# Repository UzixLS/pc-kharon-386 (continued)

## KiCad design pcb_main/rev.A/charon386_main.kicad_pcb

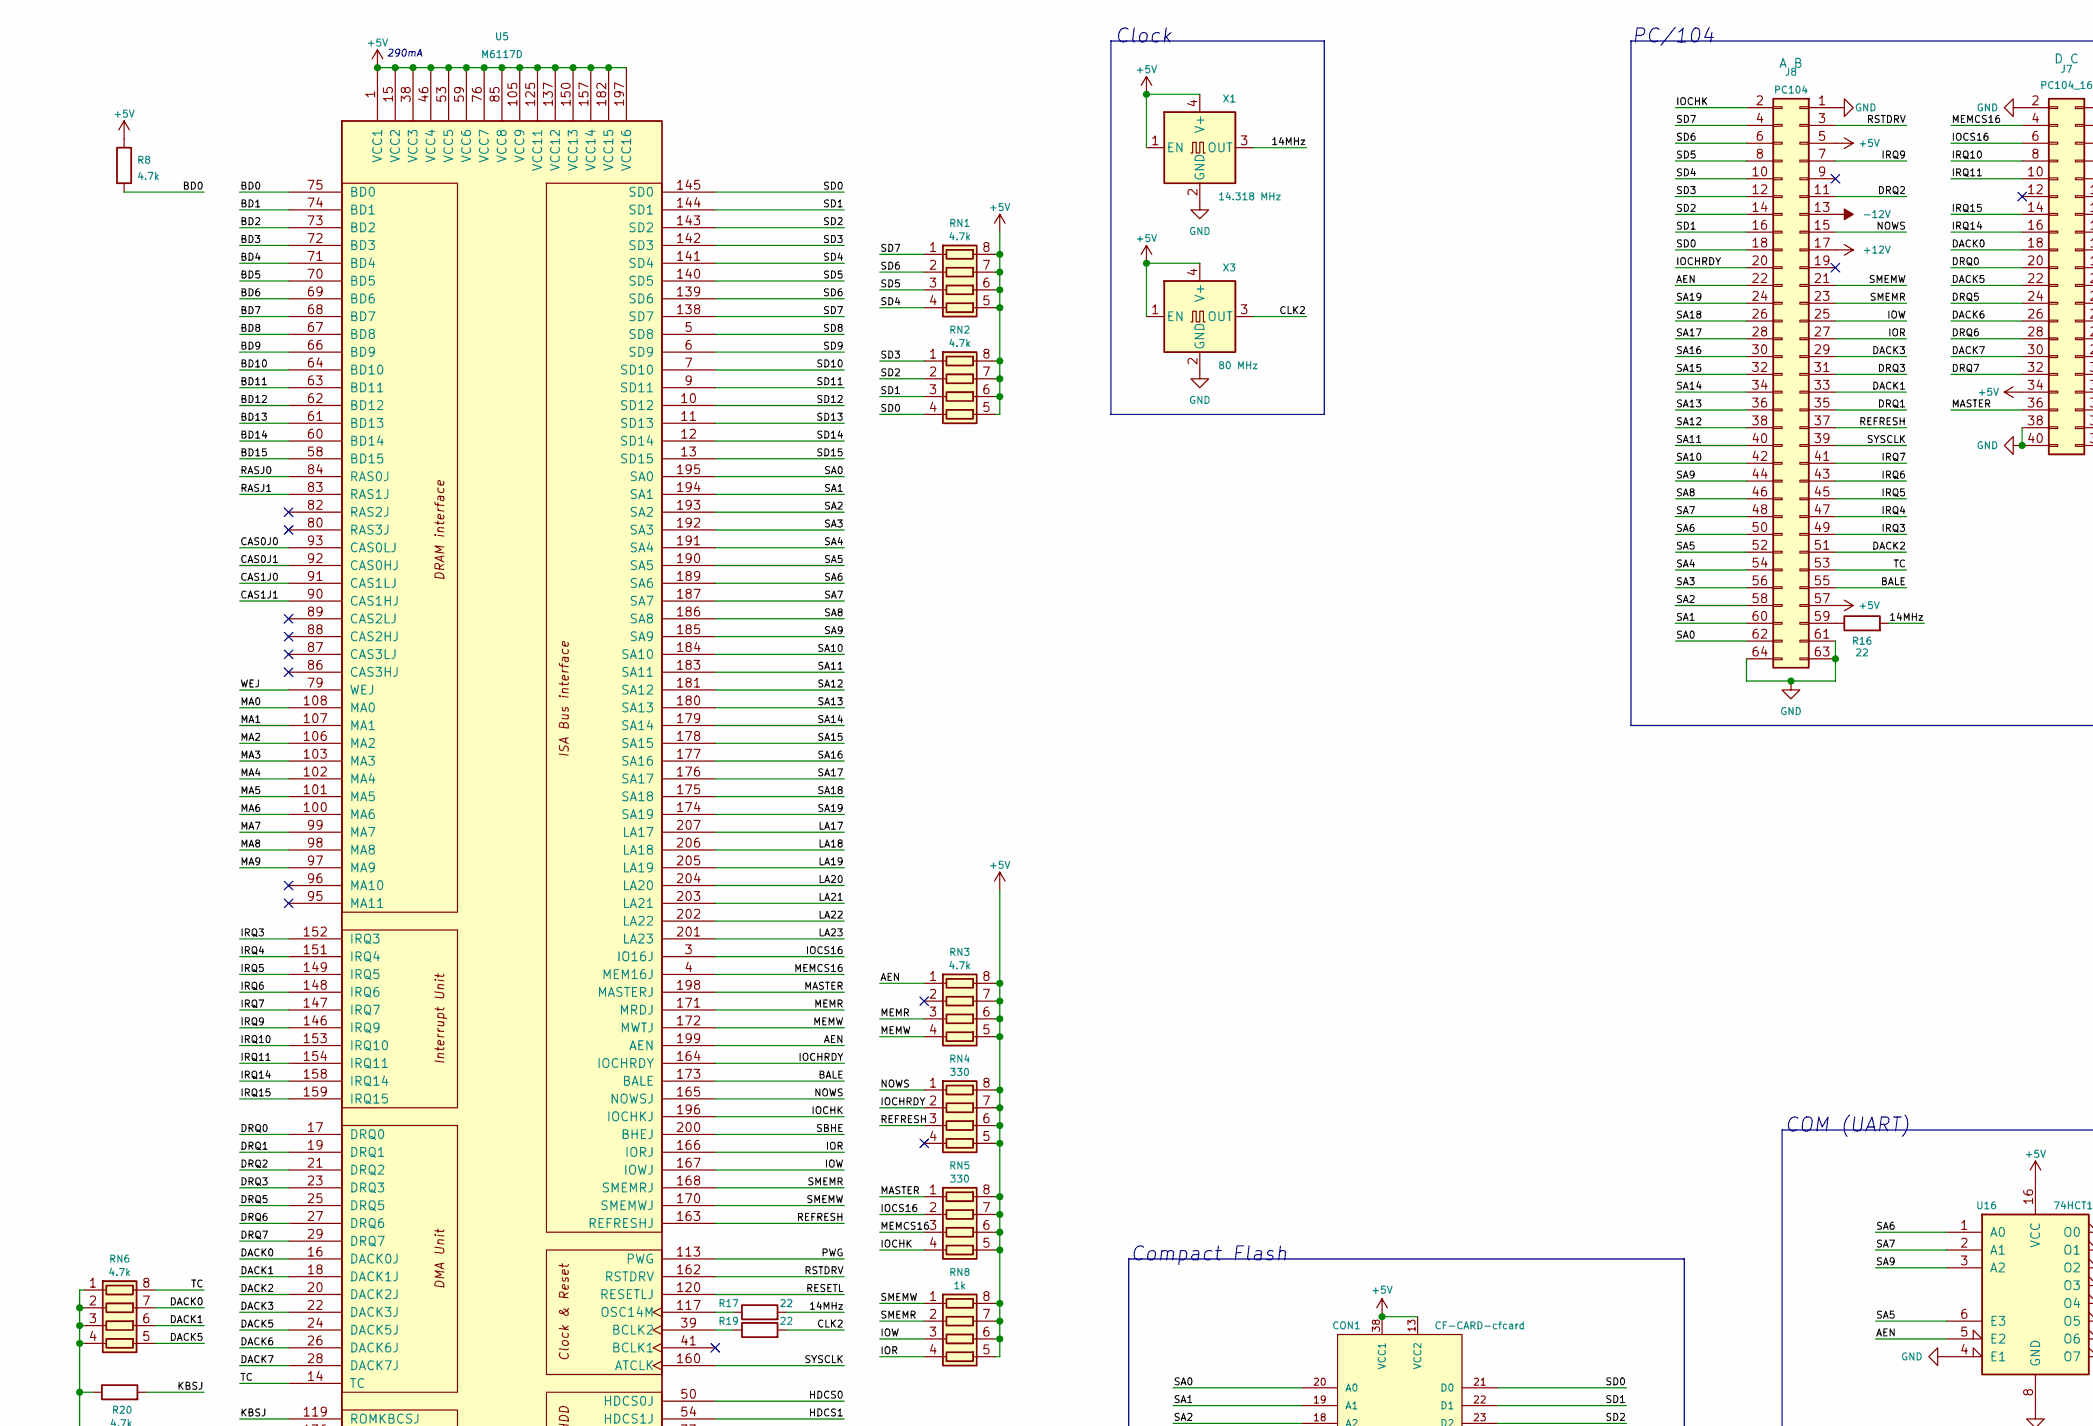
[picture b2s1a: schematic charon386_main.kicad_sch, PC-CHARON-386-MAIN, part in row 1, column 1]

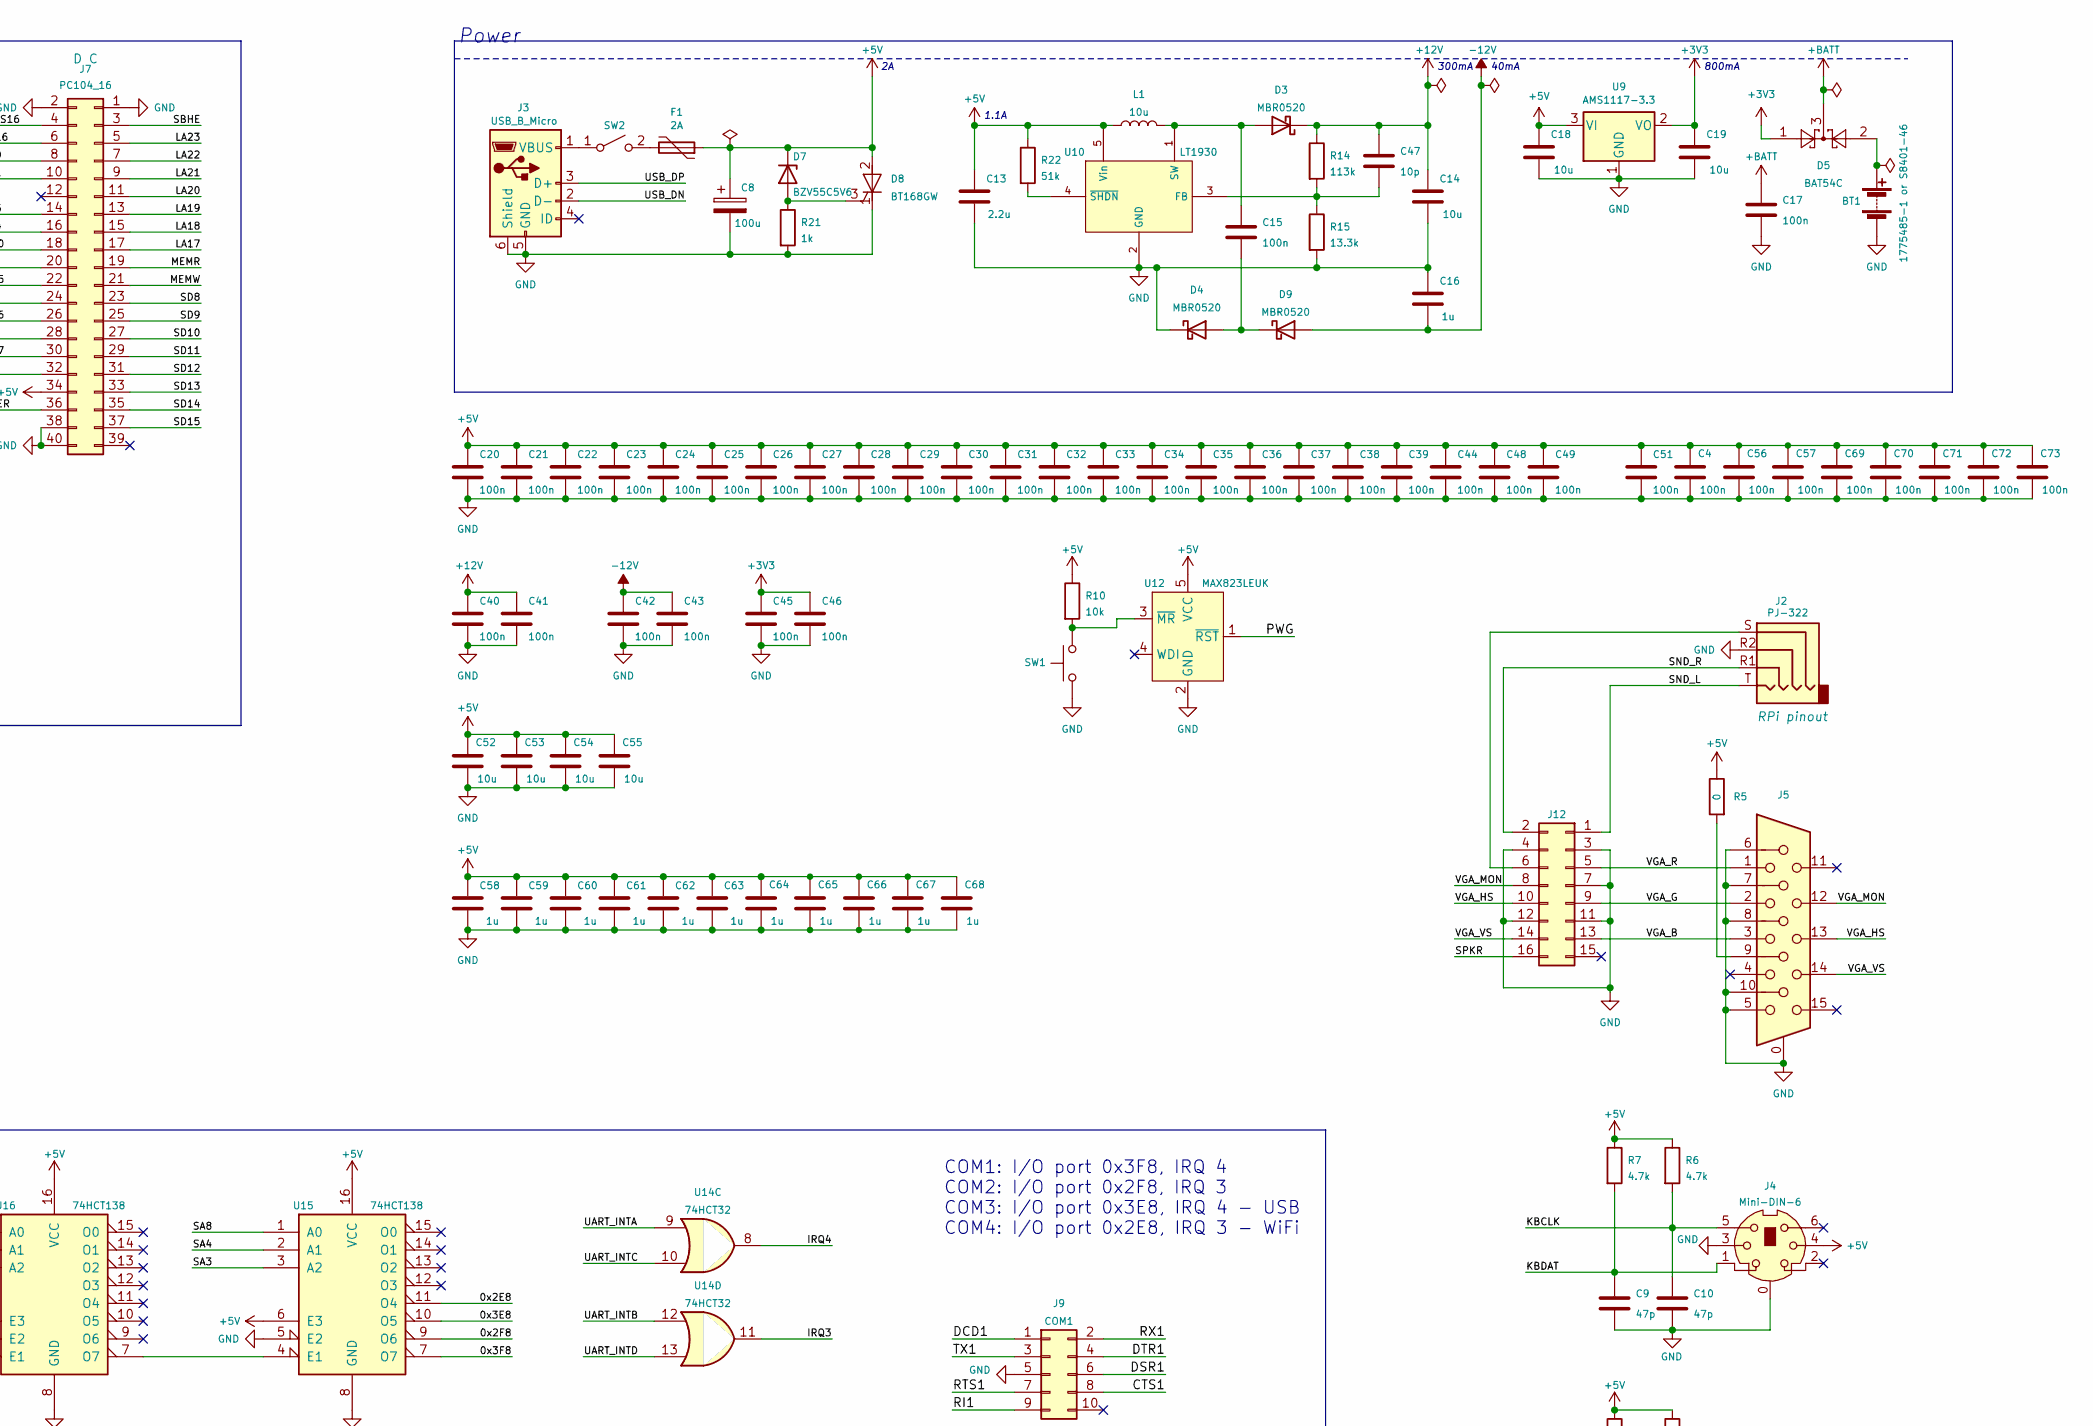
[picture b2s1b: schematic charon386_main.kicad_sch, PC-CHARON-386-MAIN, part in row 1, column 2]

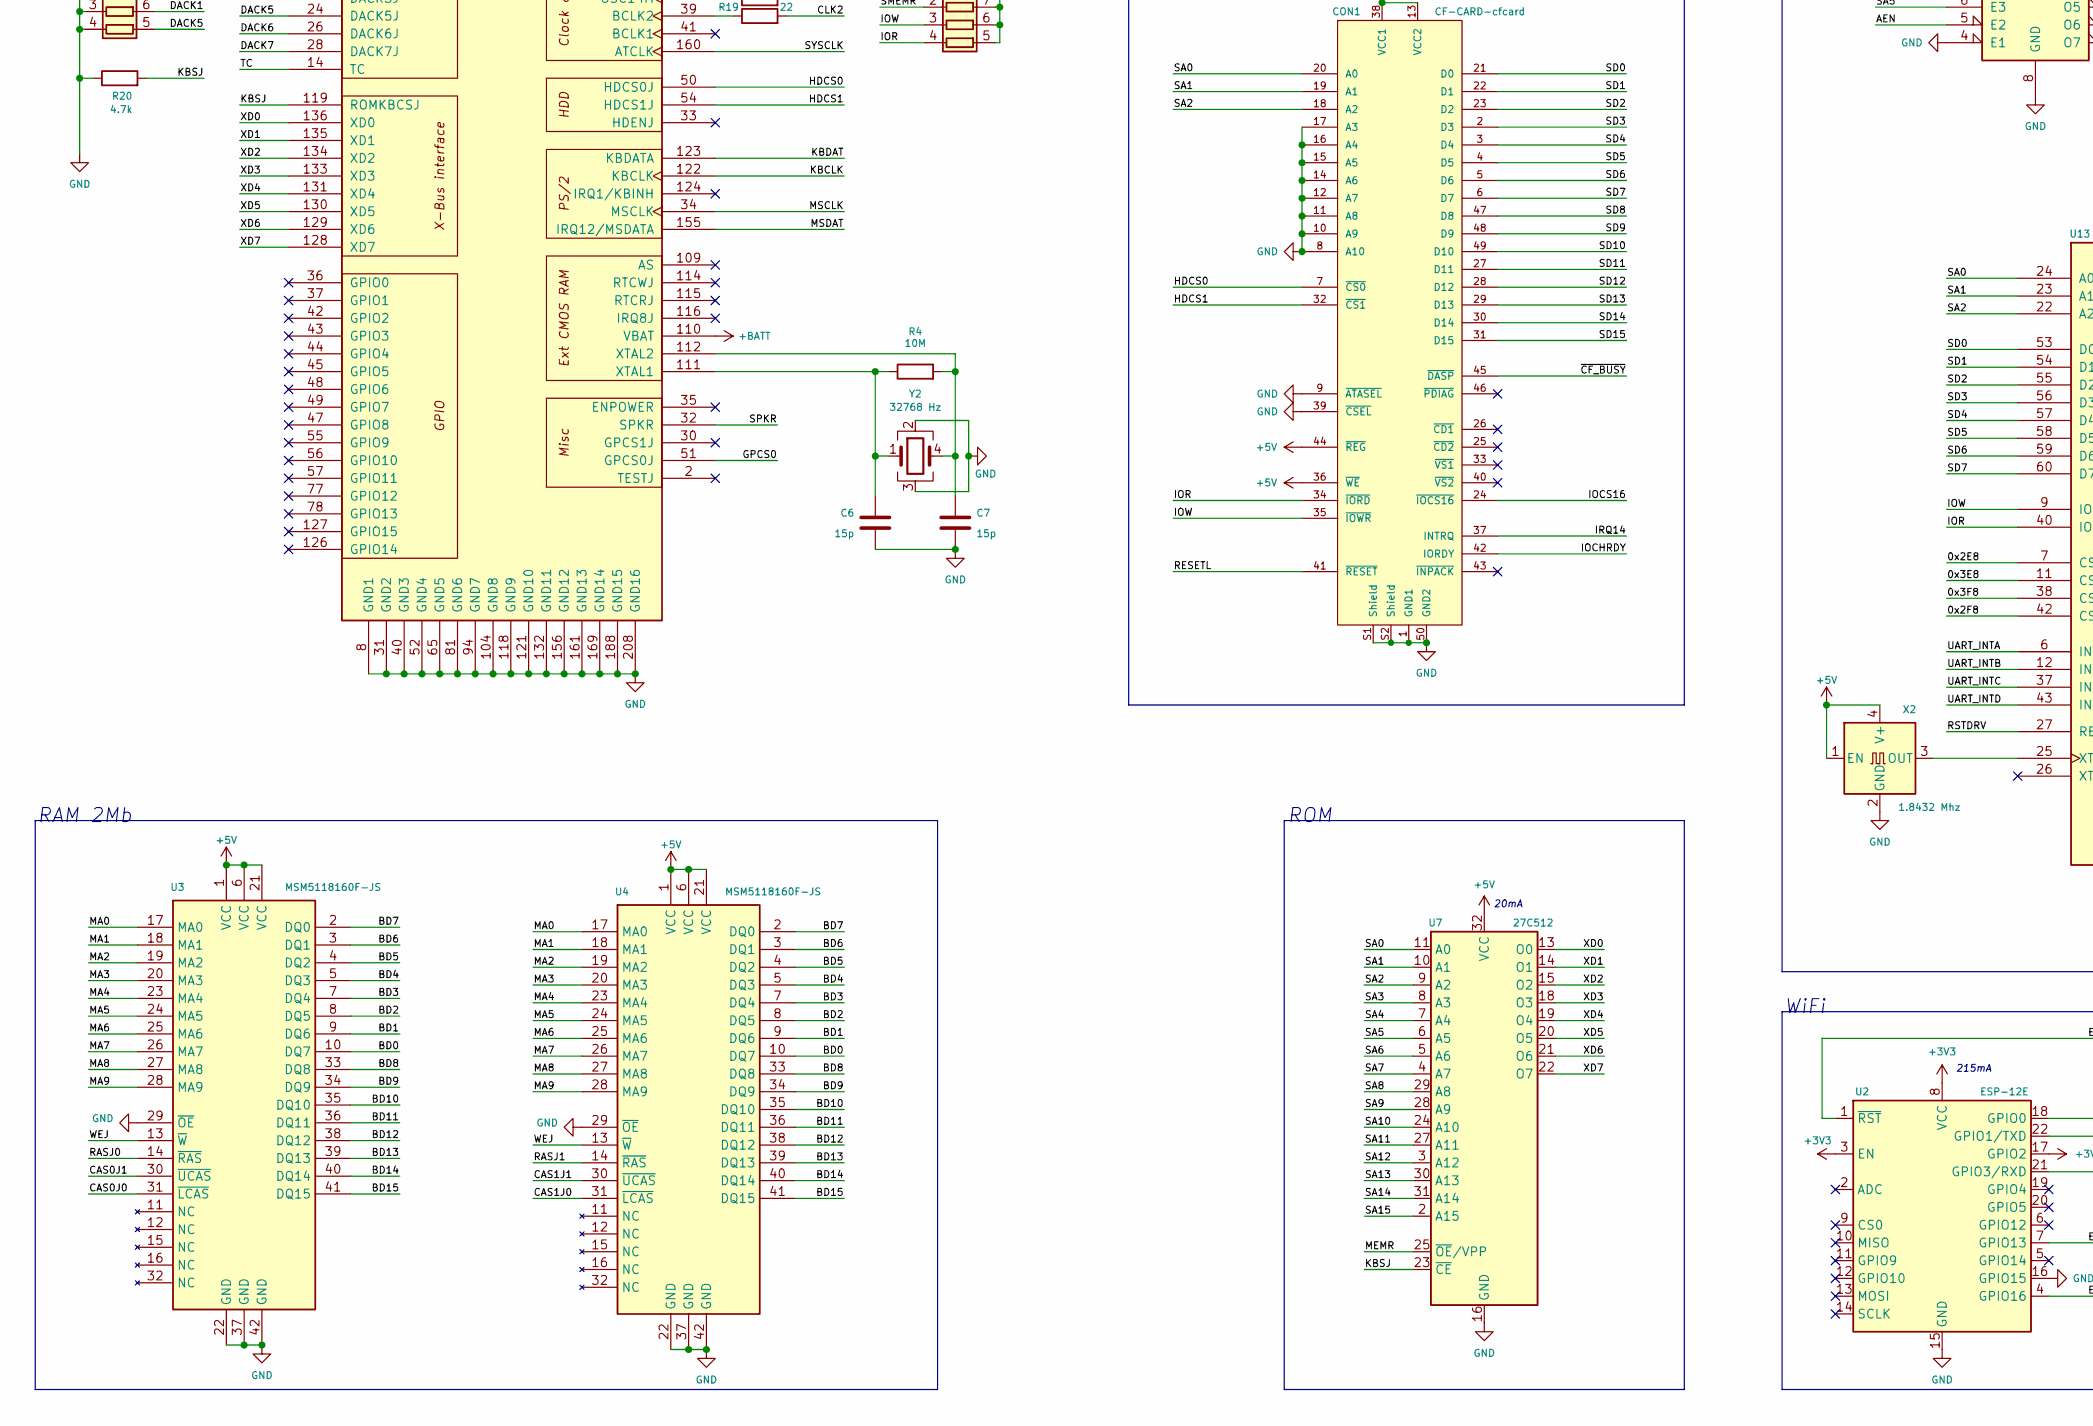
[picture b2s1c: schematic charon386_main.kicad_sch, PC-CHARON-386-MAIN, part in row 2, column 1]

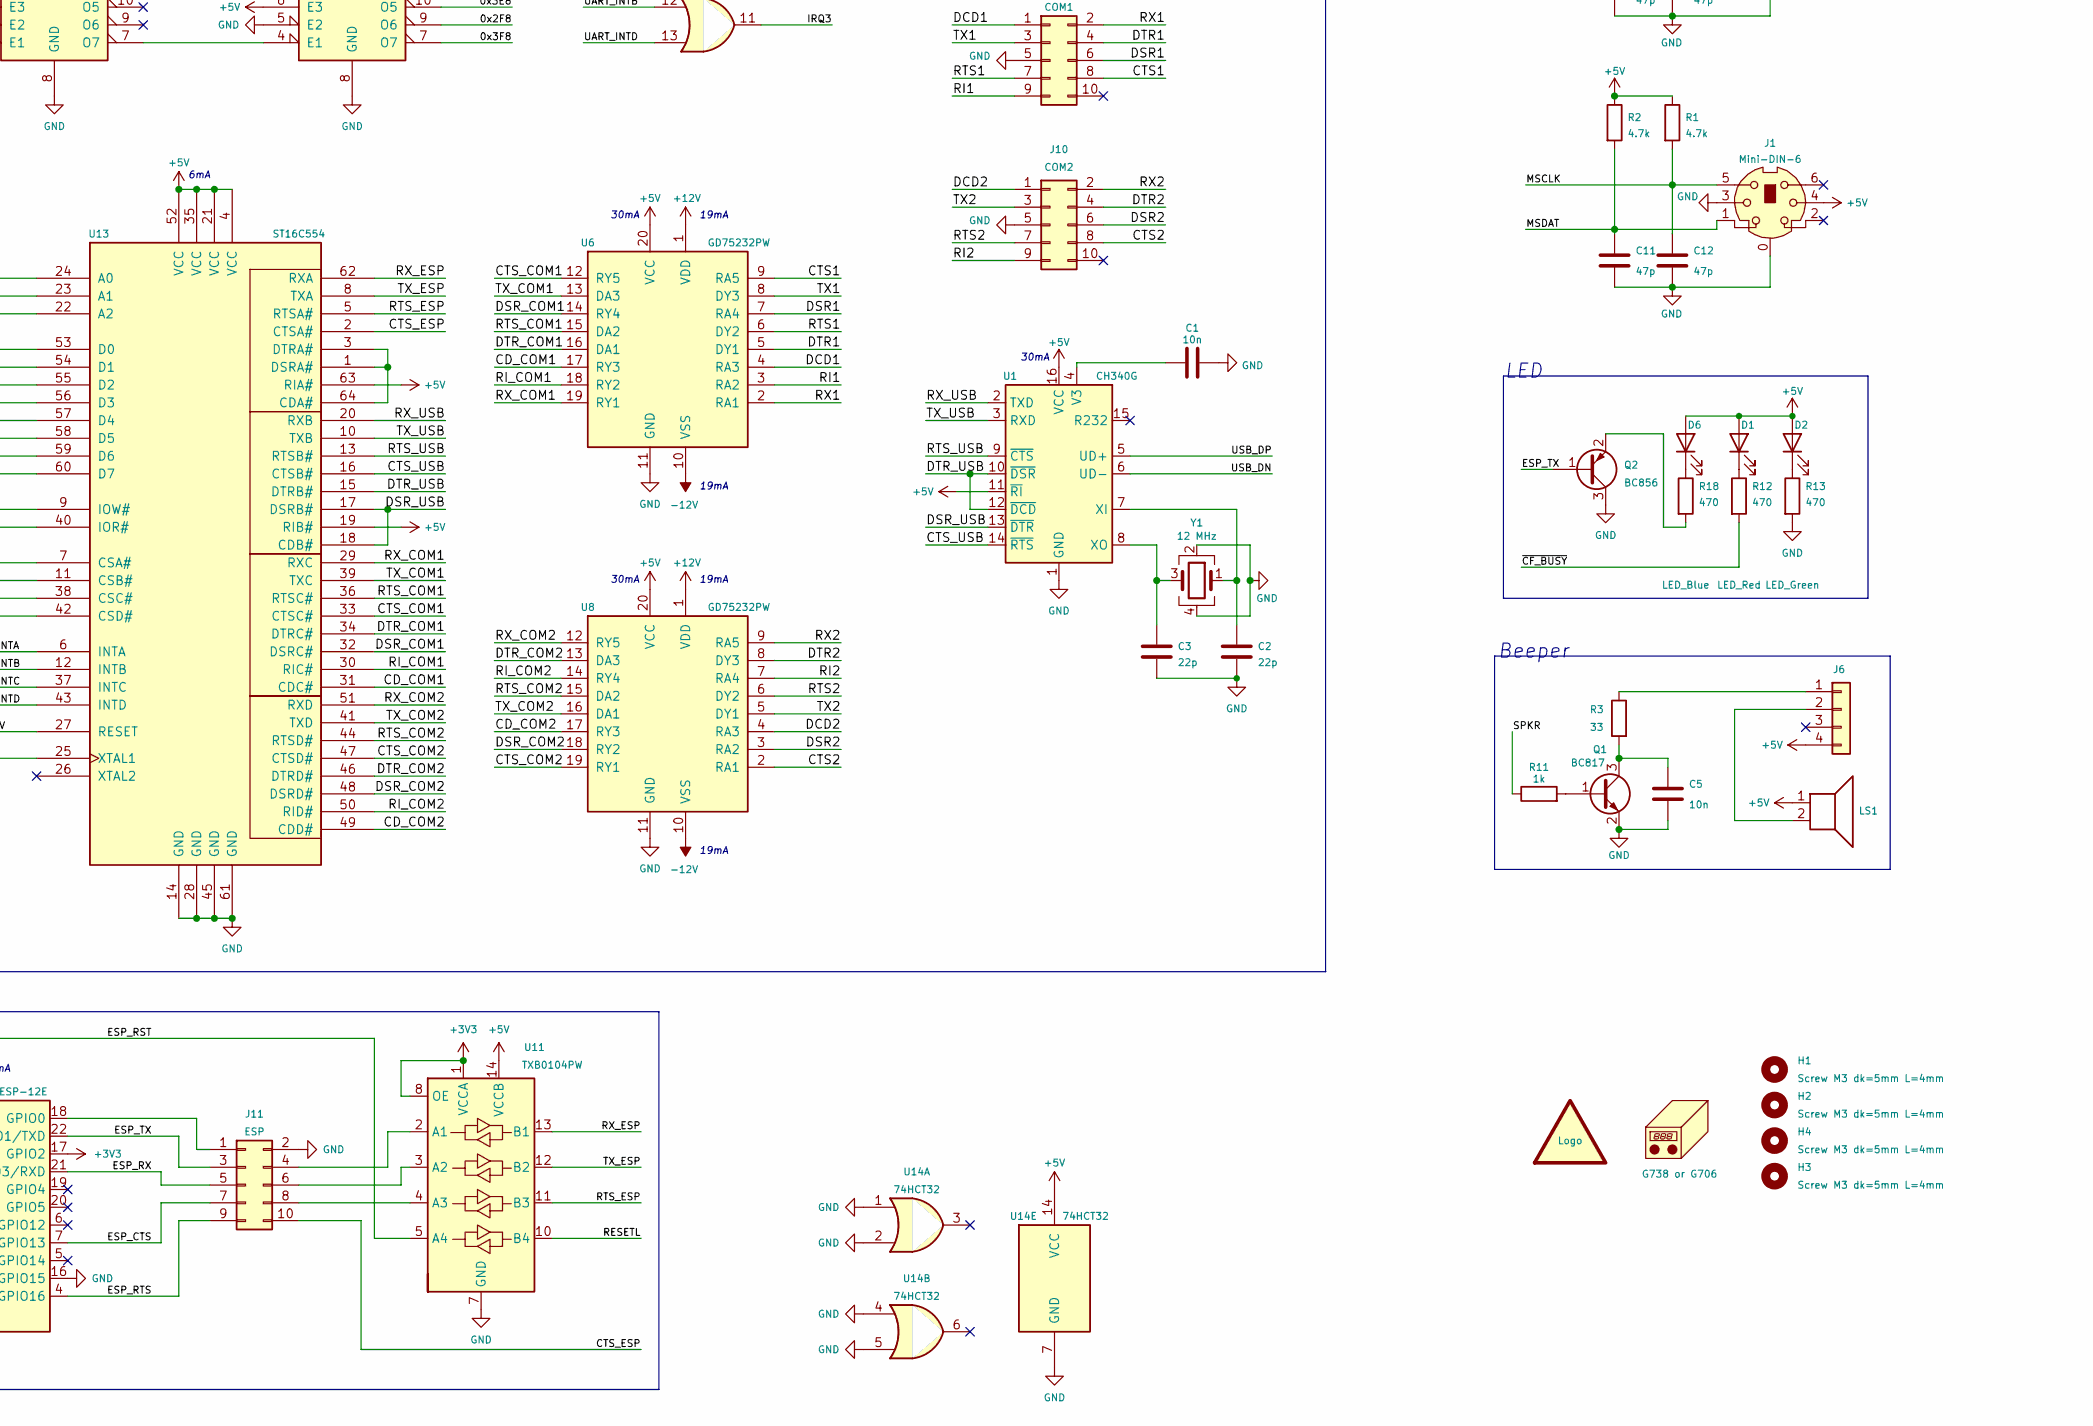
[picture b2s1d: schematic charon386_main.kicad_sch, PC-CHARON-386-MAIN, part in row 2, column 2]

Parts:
BT1: 1775485-1 or S8401-46; CR2032V
C1, C5: 10n; C_0603_1608Metric_Pad1.08x0.95mm_HandSolder
C2, C3: 22p; C_0603_1608Metric_Pad1.08x0.95mm_HandSolder
C4, C17, C20, C21, C22, C23, C24, C25, C26, C27, C28, C29, C30, C31, C32, C33, C34, C35, C36, C37, C38, C39, C40, C41, C42, C43, C44, C45, C46, C48, C49, C51, C56, C57, C69, C70, C71, C72, C73: 100n; C_0603_1608Metric_Pad1.08x0.95mm_HandSolder
C6, C7: 15p; C_0603_1608Metric_Pad1.08x0.95mm_HandSolder
C8: 100u; CP_EIA-7343-31_Kemet-D_Pad2.25x2.55mm_HandSolder
C9, C10, C11, C12: 47p; C_0603_1608Metric_Pad1.08x0.95mm_HandSolder
C13: 2.2u; C_0805_2012Metric_Pad1.18x1.45mm_HandSolder
C14, C18, C19, C52, C53, C54, C55: 10u; C_0805_2012Metric_Pad1.18x1.45mm_HandSolder
C15: 100n; C_0805_2012Metric_Pad1.18x1.45mm_HandSolder
C16: 1u; C_0805_2012Metric_Pad1.18x1.45mm_HandSolder
C47: 10p; C_0603_1608Metric_Pad1.08x0.95mm_HandSolder
C58, C59, C60, C61, C62, C63, C64, C65, C66, C67, C68: 1u; C_0603_1608Metric_Pad1.08x0.95mm_HandSolder
CON1: CF-CARD-cfcard; TE_1734451-1-LONG
D1: LED_Red; LED_D3.0mm_Horizontal_O1.27mm_Z6.0mm
D2: LED_Green; LED_D3.0mm_Horizontal_O1.27mm_Z6.0mm
D3, D4, D9: MBR0520; D_SOD-123
D5: BAT54C; SOT-23
D6: LED_Blue; LED_D3.0mm_Horizontal_O1.27mm_Z6.0mm
D7: BZV55C5V6; D_MiniMELF
D8: BT168GW; SOT-223-3_TabPin2
F1: 2A; Fuse_1812_4532Metric_Pad1.30x3.40mm_HandSolder
H1, H2, H3, H4: Screw M3 dk=5mm L=4mm; MountingHole_3.2mm_M3_dk5.2mm_Mask
J1, J4: Mini-DIN-6; minidin-6
J2: PJ-322
J3: USB_B_Micro; USB_Micro-B_Molex-105017-0001
J5: DB15_Female_HighDensity_MountingHoles; DSUB-15-HD_Female_Horizontal_P2.29x1.98mm_EdgePinOffset3.03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
J6: Conn_01x04; PinHeader_1x04_P2.54mm_Vertical
J7: PC104_16; PinSocket_2x20_P2.54mm_Vertical
J8: PC104; PinSocket_2x32_P2.54mm_Vertical
J9: COM1; PinHeader_2x05_P2.54mm_Vertical
J10: COM2; PinHeader_2x05_P2.54mm_Vertical
J11: ESP; PinHeader_2x05_P2.54mm_Vertical
J12: Conn_02x07_Odd_Even; PinSocket_2x08_P2.54mm_Vertical
L1: 10u; L_Taiyo-Yuden_NR-60xx_HandSoldering
LOGO1: graphic; black-mage-12.5x8.6
LS1: Speaker; Buzzer_12x9.5RM7.6
N1: G738 or G706
Q1: BC817; SOT-23
Q2: BC856; SOT-23
R1, R2, R6, R7, R8, R20: 4.7k; R_0603_1608Metric_Pad0.98x0.95mm_HandSolder
R3: 33; R_0805_2012Metric_Pad1.20x1.40mm_HandSolder
R4: 10M; R_0603_1608Metric_Pad0.98x0.95mm_HandSolder
R5: 0; R_0603_1608Metric_Pad0.98x0.95mm_HandSolder
R10: 10k; R_0603_1608Metric_Pad0.98x0.95mm_HandSolder
R11, R21: 1k; R_0603_1608Metric_Pad0.98x0.95mm_HandSolder
R12, R13, R18: 470; R_0603_1608Metric_Pad0.98x0.95mm_HandSolder
R14: 113k; R_0603_1608Metric_Pad0.98x0.95mm_HandSolder
R15: 13.3k; R_0603_1608Metric_Pad0.98x0.95mm_HandSolder
R16, R17, R19: 22; R_0603_1608Metric_Pad0.98x0.95mm_HandSolder
R22: 51k; R_0603_1608Metric_Pad0.98x0.95mm_HandSolder
RN1, RN2, RN3, RN6: 4.7k; R_Array_Convex_4x0603
RN4, RN5: 330; R_Array_Convex_4x0603
RN8: 1k; R_Array_Convex_4x0603
SW1: SW_Push; SW_Tactile_SPST_Angled_PTS645Vx83-2LFS
SW2: Jumper / Pin header 1x2 Pitch=2.54mm; Molex_KK-254_AE-6410-02A_1x02_P2.54mm_Vertical
U1: CH340G; SOIC-16_3.9x9.9mm_P1.27mm
U2: ESP-12E
U3, U4: MSM5118160F-JS; SOJ-42
U5: M6117D; PQFP-208_28x28mm_P0.5mm
U6, U8: GD75232PW; TSSOP-20_4.4x6.5mm_P0.65mm
U7: 27C512; PLCC-32_11.4x14.0mm_P1.27mm-longpads
U9: AMS1117-3.3; SOT-223-3_TabPin2
U10: LT1930; SOT-23-5_HandSoldering
U11: TXB0104PW; TSSOP-14_4.4x5mm_P0.65mm
U12: MAX823LEUK; SOT-23-5
U13: ST16C554; LQFP-64_10x10mm_P0.5mm
U14: 74HCT32; TSSOP-14_4.4x5mm_P0.65mm
U15, U16: 74HCT138; TSSOP-16_4.4x5mm_P0.65mm
X1: 14.318 MHz; Oscillator_SMD_SeikoEpson_SG8002CA-4Pin_7.0x5.0mm
X2: 1.8432 Mhz; Oscillator_SMD_SeikoEpson_SG8002CA-4Pin_7.0x5.0mm
X3: 80 MHz; Oscillator_SMD_SeikoEpson_SG8002CA-4Pin_7.0x5.0mm
Y1: 12 MHz; Crystal_SMD_SeikoEpson_TSX3225-4Pin_3.2x2.5mm_HandSoldering
Y2: 32768 Hz; Crystal_SMD_SeikoEpson_MC306-4Pin_8.0x3.2mm_HandSoldering

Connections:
+3V3: C19.2, C45.2, C46.2, D5.1, U2.3 (EN), U2.8 (VCC), U2.17 (GPIO2), U9.2 (VO), U11.1 (VCCA), U11.8 (OE)
+5V: C4.1, C8.1, C13.2, C18.2, C20.2, C21.2, C22.2, C23.2, C24.2, C25.2, C26.2, C27.2, C28.2, C29.2, C30.2, C31.2, C32.2, C33.2, C34.2, C35.2, C36.2, C37.2, C38.2, C39.2, C44.2, C48.2, C49.2, C51.2, C52.1, C53.1, C54.1, C55.1, C56.1, C57.1, C58.2, C59.2, C60.2, C61.2, C62.2, C63.2, C64.1, C65.1, C66.1, C67.1, C68.1, C69.1, C70.1, C71.1, C72.1, C73.1, CON1.13 (VCC2), CON1.36 (~WE), CON1.38 (VCC1), CON1.44 (~REG), D1.2 (A), D2.2 (A), D6.2 (A), D7.1 (K), D8.2 (A), F1.1, J1.4, J4.4, J6.4, J7.34, J8.5, J8.57, L1.1, LS1.1, R1.1, R2.1, R5.1, R6.1, R7.1, R8.1, R10.1, R22.1, RN1.5 (R4.2), RN1.6 (R3.2), RN1.7 (R2.2), RN1.8 (R1.2), RN2.5 (R4.2), RN2.6 (R3.2), RN2.7 (R2.2), RN2.8 (R1.2), RN3.5 (R4.2), RN3.6 (R3.2), RN3.7 (R2.2), RN3.8 (R1.2), RN4.5 (R4.2), RN4.6 (R3.2), RN4.7 (R2.2), RN4.8 (R1.2), RN5.5 (R4.2), RN5.6 (R3.2), RN5.7 (R2.2), RN5.8 (R1.2), RN8.5 (R4.2), RN8.6 (R3.2), RN8.7 (R2.2), RN8.8 (R1.2), U1.11 (~RI), U1.16 (VCC), U3.1 (VCC), U3.6 (VCC), U3.21 (VCC), U4.1 (VCC), U4.6 (VCC), U4.21 (VCC), U5.1 (VCC1), U5.15 (VCC2), U5.38 (VCC3), U5.46 (VCC4), U5.53 (VCC5), U5.59 (VCC6), U5.76 (VCC7), U5.85 (VCC8), U5.105 (VCC9), U5.125 (VCC11), U5.137 (VCC12), U5.150 (VCC13), U5.157 (VCC14), U5.182 (VCC15), U5.197 (VCC16), U6.20 (VCC), U7.32 (VCC), U8.20 (VCC), U9.3 (VI), U10.5 (Vin), U11.14 (VCCB), U12.5 (VCC), U13.4 (VCC), U13.19 (RIB#), U13.21 (VCC), U13.35 (VCC), U13.52 (VCC), U13.63 (RIA#), U14.14 (VCC), U15.6 (E3), U15.16 (VCC), U16.16 (VCC), X1.1 (EN), X1.4 (V+), X2.1 (EN), X2.4 (V+), X3.1 (EN), X3.4 (V+)
+12V: C14.2, C40.2, C41.2, C47.1, D3.1 (K), J8.17, R14.1, U6.1 (VDD), U8.1 (VDD)
+BATT: C17.1, D5.3, U5.110 (VBAT)
-12V: C16.1, C42.2, C43.2, D9.2 (A), J8.13, U6.10 (VSS), U8.10 (VSS)
/0x2E8: U13.7 (CSA#), U15.11 (O4)
/0x2F8: U13.42 (CSD#), U15.9 (O6)
/0x3E8: U13.11 (CSB#), U15.10 (O5)
/0x3F8: U13.38 (CSC#), U15.7 (O7)
/14MHz: R16.2, R17.2, X1.3 (OUT)
/AEN: J8.22, RN3.1 (R1.1), U5.199 (AEN), U16.5 (E2)
/BALE: J8.55, U5.173 (BALE)
/BD0: R8.2, U3.10 (DQ7), U4.10 (DQ7), U5.75 (BD0)
/BD1: U3.9 (DQ6), U4.9 (DQ6), U5.74 (BD1)
/BD2: U3.8 (DQ5), U4.8 (DQ5), U5.73 (BD2)
/BD3: U3.7 (DQ4), U4.7 (DQ4), U5.72 (BD3)
/BD4: U3.5 (DQ3), U4.5 (DQ3), U5.71 (BD4)
/BD5: U3.4 (DQ2), U4.4 (DQ2), U5.70 (BD5)
/BD6: U3.3 (DQ1), U4.3 (DQ1), U5.69 (BD6)
/BD7: U3.2 (DQ0), U4.2 (DQ0), U5.68 (BD7)
/BD8: U3.33 (DQ8), U4.33 (DQ8), U5.67 (BD8)
/BD9: U3.34 (DQ9), U4.34 (DQ9), U5.66 (BD9)
/BD10: U3.35 (DQ10), U4.35 (DQ10), U5.64 (BD10)
/BD11: U3.36 (DQ11), U4.36 (DQ11), U5.63 (BD11)
/BD12: U3.38 (DQ12), U4.38 (DQ12), U5.62 (BD12)
/BD13: U3.39 (DQ13), U4.39 (DQ13), U5.61 (BD13)
/BD14: U3.40 (DQ14), U4.40 (DQ14), U5.60 (BD14)
/BD15: U3.41 (DQ15), U4.41 (DQ15), U5.58 (BD15)
/CAS0J0: U3.31 (~LCAS), U5.93 (CAS0LJ)
/CAS0J1: U3.30 (~UCAS), U5.92 (CAS0HJ)
/CAS1J0: U4.31 (~LCAS), U5.91 (CAS1LJ)
/CAS1J1: U4.30 (~UCAS), U5.90 (CAS1HJ)
/CD_COM1: U6.17 (RY3), U13.31 (CDC#)
/CD_COM2: U8.17 (RY3), U13.49 (CDD#)
/CLK2: R19.2, X3.3 (OUT)
/CTS1: J9.8, U6.9 (RA5)
/CTS2: J10.8, U8.2 (RA1)
/CTS_COM1: U6.12 (RY5), U13.33 (CTSC#)
/CTS_COM2: U8.19 (RY1), U13.47 (CTSD#)
/CTS_ESP: J11.10, U13.2 (CTSA#)
/CTS_USB: U1.14 (~RTS), U13.16 (CTSB#)
/DACK0: J7.18, RN6.7 (R2.2), U5.16 (DACK0J)
/DACK1: J8.33, RN6.6 (R3.2), U5.18 (DACK1J)
/DACK2: J8.51, U5.20 (DACK2J)
/DACK3: J8.29, U5.22 (DACK3J)
/DACK5: J7.22, RN6.5 (R4.2), U5.24 (DACK5J)
/DACK6: J7.26, U5.26 (DACK6J)
/DACK7: J7.30, U5.28 (DACK7J)
/DCD1: J9.1, U6.4 (RA3)
/DCD2: J10.1, U8.4 (RA3)
/DRQ0: J7.20, U5.17 (DRQ0)
/DRQ1: J8.35, U5.19 (DRQ1)
/DRQ2: J8.11, U5.21 (DRQ2)
/DRQ3: J8.31, U5.23 (DRQ3)
/DRQ5: J7.24, U5.25 (DRQ5)
/DRQ6: J7.28, U5.27 (DRQ6)
/DRQ7: J7.32, U5.29 (DRQ7)
/DSR1: J9.6, U6.7 (RA4)
/DSR2: J10.6, U8.3 (RA2)
/DSR_COM1: U6.14 (RY4), U13.32 (DSRC#)
/DSR_COM2: U8.18 (RY2), U13.48 (DSRD#)
/DSR_USB: U1.13 (~DTR), U13.17 (DSRB#), U13.18 (CDB#)
/DTR1: J9.4, U6.5 (DY1)
/DTR2: J10.4, U8.8 (DY3)
/DTR_COM1: U6.16 (DA1), U13.34 (DTRC#)
/DTR_COM2: U8.13 (DA3), U13.46 (DTRD#)
/DTR_USB: U1.10 (~DSR), U1.12 (~DCD), U13.15 (DTRB#)
/ESP_CTS: J11.7, U2.7 (GPIO13)
/ESP_RST: U2.1 (~RST), U11.5 (A4)
/ESP_RTS: J11.9, U2.4 (GPIO16)
/ESP_RX: J11.5, U2.21 (GPIO3/RXD)
/ESP_TX: J11.3, Q2.1 (B), U2.22 (GPIO1/TXD)
/GPCS0: U5.51 (GPCS0J)
/HDCS0: CON1.7 (~CS0), U5.50 (HDCS0J)
/HDCS1: CON1.32 (~CS1), U5.54 (HDCS1J)
/IOCHK: J8.2, RN5.4 (R4.1), U5.196 (IOCHKJ)
/IOCHRDY: CON1.42 (IORDY), J8.20, RN4.2 (R2.1), U5.164 (IOCHRDY)
/IOCS16: CON1.24 (~IOCS16), J7.6, RN5.2 (R2.1), U5.3 (IO16J)
/IOR: CON1.34 (~IORD), J8.27, RN8.4 (R4.1), U5.166 (IORJ), U13.40 (IOR#)
/IOW: CON1.35 (~IOWR), J8.25, RN8.3 (R3.1), U5.167 (IOWJ), U13.9 (IOW#)
/IRQ3: J8.49, U5.152 (IRQ3), U14.11
/IRQ4: J8.47, U5.151 (IRQ4), U14.8
/IRQ5: J8.45, U5.149 (IRQ5)
/IRQ6: J8.43, U5.148 (IRQ6)
/IRQ7: J8.41, U5.147 (IRQ7)
/IRQ9: J8.7, U5.146 (IRQ9)
/IRQ10: J7.8, U5.153 (IRQ10)
/IRQ11: J7.10, U5.154 (IRQ11)
/IRQ14: CON1.37 (INTRQ), J7.16, U5.158 (IRQ14)
/IRQ15: J7.14, U5.159 (IRQ15)
/KBCLK: C10.1, J4.5, R6.2, U5.122 (KBCLK)
/KBDAT: C9.1, J4.1, R7.2, U5.123 (KBDATA)
/KBSJ: R20.2, U5.119 (ROMKBCSJ), U7.23 (~CE)
/LA17: J7.17, U5.207 (LA17)
/LA18: J7.15, U5.206 (LA18)
/LA19: J7.13, U5.205 (LA19)
/LA20: J7.11, U5.204 (LA20)
/LA21: J7.9, U5.203 (LA21)
/LA22: J7.7, U5.202 (LA22)
/LA23: J7.5, U5.201 (LA23)
/MA0: U3.17 (MA0), U4.17 (MA0), U5.108 (MA0)
/MA1: U3.18 (MA1), U4.18 (MA1), U5.107 (MA1)
/MA2: U3.19 (MA2), U4.19 (MA2), U5.106 (MA2)
/MA3: U3.20 (MA3), U4.20 (MA3), U5.103 (MA3)
/MA4: U3.23 (MA4), U4.23 (MA4), U5.102 (MA4)
/MA5: U3.24 (MA5), U4.24 (MA5), U5.101 (MA5)
/MA6: U3.25 (MA6), U4.25 (MA6), U5.100 (MA6)
/MA7: U3.26 (MA7), U4.26 (MA7), U5.99 (MA7)
/MA8: U3.27 (MA8), U4.27 (MA8), U5.98 (MA8)
/MA9: U3.28 (MA9), U4.28 (MA9), U5.97 (MA9)
/MASTER: J7.36, RN5.1 (R1.1), U5.198 (MASTERJ)
/MEMCS16: J7.4, RN5.3 (R3.1), U5.4 (MEM16J)
/MEMR: J7.19, RN3.3 (R3.1), U5.171 (MRDJ), U7.25 (~OE/VPP)
/MEMW: J7.21, RN3.4 (R4.1), U5.172 (MWTJ)
/MSCLK: C12.1, J1.5, R1.2, U5.34 (MSCLK)
/MSDAT: C11.1, J1.1, R2.2, U5.155 (IRQ12/MSDATA)
/NOWS: J8.15, RN4.1 (R1.1), U5.165 (NOWSJ)
/PWG: U5.113 (PWG), U12.1 (~RST)
/RASJ0: U3.14 (~RAS), U5.84 (RAS0J)
/RASJ1: U4.14 (~RAS), U5.83 (RAS1J)
/REFRESH: J8.37, RN4.3 (R3.1), U5.163 (REFRESHJ)
/RESETL: CON1.41 (~RESET), U5.120 (RESETLJ), U11.10 (B4)
/RI1: J9.9, U6.3 (RA2)
/RI2: J10.9, U8.7 (RA4)
/RI_COM1: U6.18 (RY2), U13.30 (RIC#)
/RI_COM2: U8.14 (RY4), U13.50 (RID#)
/RSTDRV: J8.3, U5.162 (RSTDRV), U13.27 (RESET)
/RTS1: J9.7, U6.6 (DY2)
/RTS2: J10.7, U8.6 (DY2)
/RTS_COM1: U6.15 (DA2), U13.36 (RTSC#)
/RTS_COM2: U8.15 (DA2), U13.44 (RTSD#)
/RTS_ESP: U11.11 (B3), U13.5 (RTSA#)
/RTS_USB: U1.9 (~CTS), U13.13 (RTSB#)
/RX1: J9.2, U6.2 (RA1)
/RX2: J10.2, U8.9 (RA5)
/RX_COM1: U6.19 (RY1), U13.29 (RXC)
/RX_COM2: U8.12 (RY5), U13.51 (RXD)
/RX_ESP: U11.13 (B1), U13.62 (RXA)
/RX_USB: U1.2 (TXD), U13.20 (RXB)
/SA0: CON1.20 (A0), J8.62, U5.195 (SA0), U7.11 (A0), U13.24 (A0)
/SA1: CON1.19 (A1), J8.60, U5.194 (SA1), U7.10 (A1), U13.23 (A1)
/SA2: CON1.18 (A2), J8.58, U5.193 (SA2), U7.9 (A2), U13.22 (A2)
/SA3: J8.56, U5.192 (SA3), U7.8 (A3), U15.3 (A2)
/SA4: J8.54, U5.191 (SA4), U7.7 (A4), U15.2 (A1)
/SA5: J8.52, U5.190 (SA5), U7.6 (A5), U16.6 (E3)
/SA6: J8.50, U5.189 (SA6), U7.5 (A6), U16.1 (A0)
/SA7: J8.48, U5.187 (SA7), U7.4 (A7), U16.2 (A1)
/SA8: J8.46, U5.186 (SA8), U7.29 (A8), U15.1 (A0)
/SA9: J8.44, U5.185 (SA9), U7.28 (A9), U16.3 (A2)
/SA10: J8.42, U5.184 (SA10), U7.24 (A10)
/SA11: J8.40, U5.183 (SA11), U7.27 (A11)
/SA12: J8.38, U5.181 (SA12), U7.3 (A12)
/SA13: J8.36, U5.180 (SA13), U7.30 (A13)
/SA14: J8.34, U5.179 (SA14), U7.31 (A14)
/SA15: J8.32, U5.178 (SA15), U7.2 (A15)
/SA16: J8.30, U5.177 (SA16)
/SA17: J8.28, U5.176 (SA17)
/SA18: J8.26, U5.175 (SA18)
/SA19: J8.24, U5.174 (SA19)
/SBHE: J7.3, U5.200 (BHEJ)
/SD0: CON1.21 (D0), J8.18, RN2.4 (R4.1), U5.145 (SD0), U13.53 (D0)
/SD1: CON1.22 (D1), J8.16, RN2.3 (R3.1), U5.144 (SD1), U13.54 (D1)
/SD2: CON1.23 (D2), J8.14, RN2.2 (R2.1), U5.143 (SD2), U13.55 (D2)
/SD3: CON1.2 (D3), J8.12, RN2.1 (R1.1), U5.142 (SD3), U13.56 (D3)
/SD4: CON1.3 (D4), J8.10, RN1.4 (R4.1), U5.141 (SD4), U13.57 (D4)
/SD5: CON1.4 (D5), J8.8, RN1.3 (R3.1), U5.140 (SD5), U13.58 (D5)
/SD6: CON1.5 (D6), J8.6, RN1.2 (R2.1), U5.139 (SD6), U13.59 (D6)
/SD7: CON1.6 (D7), J8.4, RN1.1 (R1.1), U5.138 (SD7), U13.60 (D7)
/SD8: CON1.47 (D8), J7.23, U5.5 (SD8)
/SD9: CON1.48 (D9), J7.25, U5.6 (SD9)
/SD10: CON1.49 (D10), J7.27, U5.7 (SD10)
/SD11: CON1.27 (D11), J7.29, U5.9 (SD11)
/SD12: CON1.28 (D12), J7.31, U5.10 (SD12)
/SD13: CON1.29 (D13), J7.33, U5.11 (SD13)
/SD14: CON1.30 (D14), J7.35, U5.12 (SD14)
/SD15: CON1.31 (D15), J7.37, U5.13 (SD15)
/SMEMR: J8.23, RN8.2 (R2.1), U5.168 (SMEMRJ)
/SMEMW: J8.21, RN8.1 (R1.1), U5.170 (SMEMWJ)
/SND_L: J2.T, J12.1
/SND_R: J2.R1, J12.2
/SPKR: J12.16, R11.1, U5.32 (SPKR)
/SYSCLK: J8.39, U5.160 (ATCLK)
/TC: J8.53, RN6.8 (R1.2), U5.14 (TC)
/TX1: J9.3, U6.8 (DY3)
/TX2: J10.3, U8.5 (DY1)
/TX_COM1: U6.13 (DA3), U13.39 (TXC)
/TX_COM2: U8.16 (DA1), U13.41 (TXD)
/TX_ESP: U11.12 (B2), U13.8 (TXA)
/TX_USB: U1.3 (RXD), U13.10 (TXB)
/UART_INTA: U13.6 (INTA), U14.9
/UART_INTB: U13.12 (INTB), U14.12
/UART_INTC: U13.37 (INTC), U14.10
/UART_INTD: U13.43 (INTD), U14.13
/USB_DN: J3.2 (D-), U1.6 (UD-)
/USB_DP: J3.3 (D+), U1.5 (UD+)
/VGA_B: J5.3, J12.13
/VGA_G: J5.2, J12.9
/VGA_HS: J5.13, J12.10
/VGA_MON: J5.12, J12.8
/VGA_R: J5.1, J12.5
/VGA_VS: J5.14, J12.14
/WEJ: U3.13 (~W), U4.13 (~W), U5.79 (WEJ)
/XD0: U5.136 (XD0), U7.13 (O0)
/XD1: U5.135 (XD1), U7.14 (O1)
/XD2: U5.134 (XD2), U7.15 (O2)
/XD3: U5.133 (XD3), U7.18 (O3)
/XD4: U5.131 (XD4), U7.19 (O4)
/XD5: U5.130 (XD5), U7.20 (O5)
/XD6: U5.129 (XD6), U7.21 (O6)
/XD7: U5.128 (XD7), U7.22 (O7)
/~CF_BUSY: CON1.45 (~DASP), R12.2
GND: BT1.2 (-), C1.1, C2.2, C3.2, C4.2, C5.2, C6.2, C7.2, C8.2, C9.2, C10.2, C11.2, C12.2, C13.1, C14.1, C16.2, C17.2, C18.1, C19.1, C20.1, C21.1, C22.1, C23.1, C24.1, C25.1, C26.1, C27.1, C28.1, C29.1, C30.1, C31.1, C32.1, C33.1, C34.1, C35.1, C36.1, C37.1, C38.1, C39.1, C40.1, C41.1, C42.1, C43.1, C44.1, C45.1, C46.1, C48.1, C49.1, C51.1, C52.2, C53.2, C54.2, C55.2, C56.2, C57.2, C58.1, C59.1, C60.1, C61.1, C62.1, C63.1, C64.2, C65.2, C66.2, C67.2, C68.2, C69.2, C70.2, C71.2, C72.2, C73.2, CON1.1 (GND1), CON1.8 (A10), CON1.9 (~ATASEL), CON1.10 (A9), CON1.11 (A8), CON1.12 (A7), CON1.14 (A6), CON1.15 (A5), CON1.16 (A4), CON1.17 (A3), CON1.39 (~CSEL), CON1.50 (GND2), CON1.S1 (Shield), CON1.S2 (Shield), D4.1 (K), D8.1 (K), J1.0, J1.3, J2.R2, J3.5 (GND), J3.6 (Shield), J4.0, J4.3, J5.0, J5.5, J5.6, J5.7, J5.8, J5.10, J7.1, J7.2, J7.38, J7.40, J8.1, J8.61, J8.63, J8.64, J9.5, J10.5, J11.2, J12.3, J12.4, J12.7, J12.11, J12.12, Q1.2 (E), Q2.3 (C), R13.2, R15.2, R20.1, R21.2, RN6.1 (R1.1), RN6.2 (R2.1), RN6.3 (R3.1), RN6.4 (R4.1), SW1.2, U1.1 (GND), U2.15 (GND), U2.16 (GPIO15), U3.22 (GND), U3.29 (~OE), U3.37 (GND), U3.42 (GND), U4.22 (GND), U4.29 (~OE), U4.37 (GND), U4.42 (GND), U5.8 (GND1), U5.31 (GND2), U5.40 (GND3), U5.52 (GND4), U5.65 (GND5), U5.81 (GND6), U5.94 (GND7), U5.104 (GND8), U5.118 (GND9), U5.121 (GND10), U5.132 (GND11), U5.156 (GND12), U5.161 (GND13), U5.169 (GND14), U5.188 (GND15), U5.208 (GND16), U6.11 (GND), U7.16 (GND), U8.11 (GND), U9.1 (GND), U10.2 (GND), U11.7 (GND), U12.2 (GND), U13.14 (GND), U13.28 (GND), U13.45 (GND), U13.61 (GND), U14.1, U14.2, U14.4, U14.5, U14.7 (GND), U15.5 (E2), U15.8 (GND), U16.4 (E1), U16.8 (GND), X1.2 (GND), X2.2 (GND), X3.2 (GND), Y1.2, Y1.4, Y2.2, Y2.3
unnamed: BT1.1 (+), D5.2
unnamed: C1.2, U1.4 (V3)
unnamed: C2.1, U1.7 (XI), Y1.1
unnamed: C3.1, U1.8 (XO), Y1.3
unnamed: C5.1, Q1.3 (C), R3.2
unnamed: C6.1, R4.1, U5.111 (XTAL1), Y2.1
unnamed: C7.1, R4.2, U5.112 (XTAL2), Y2.4
unnamed: C15.1, D3.2 (A), L1.2, U10.1 (SW)
unnamed: C15.2, D4.2 (A), D9.1 (K)
unnamed: C47.2, R14.2, R15.1, U10.3 (FB)
unnamed: D1.1 (K), R12.1
unnamed: D2.1 (K), R13.1
unnamed: D6.1 (K), R18.1
unnamed: D7.2 (A), D8.3 (G), R21.1
unnamed: F1.2, SW2.2 (B)
unnamed: J3.1 (VBUS), SW2.1 (A)
unnamed: J5.9, R5.2
unnamed: J6.1, R3.1
unnamed: J6.2, LS1.2
unnamed: J8.59, R16.1
unnamed: J11.1, U2.18 (GPIO0)
unnamed: J11.4, U11.2 (A1)
unnamed: J11.6, U11.3 (A2)
unnamed: J11.8, U11.4 (A3)
unnamed: J2.S, J12.6
unnamed: Q1.1 (B), R11.2
unnamed: Q2.2 (E), R18.2
unnamed: R10.2, SW1.1, U12.3 (~MR)
unnamed: R17.1, U5.117 (OSC14M)
unnamed: R19.1, U5.39 (BCLK2)
unnamed: R22.2, U10.4 (~SHDN)
unnamed: U13.1 (DSRA#), U13.3 (DTRA#), U13.64 (CDA#)
unnamed: U13.25 (XTAL1), X2.3 (OUT)
unnamed: U15.4 (E1), U16.7 (O7)

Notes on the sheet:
800mA
Beeper
290mA
20mA
30mA
Power
19mA
RAM 2Mb
300mA
LED
PC/104
Clock
WiFi
ROM
6mA
40mA
COM (UART)
215mA
COM1: I/O port 0x3F8, IRQ 4 COM2: I/O port 0x2F8, IRQ 3 COM3: I/O port 0x3E8, IRQ 4 - USB COM4: I/O port 0x2E8, IRQ 3 - WiFi
Compact Flash
1.1A
